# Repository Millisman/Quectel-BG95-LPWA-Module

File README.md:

# Quectel-BG95-LPWA-Module
Quectel BG95 LPWA Module board with integrated GPS &amp; GSM

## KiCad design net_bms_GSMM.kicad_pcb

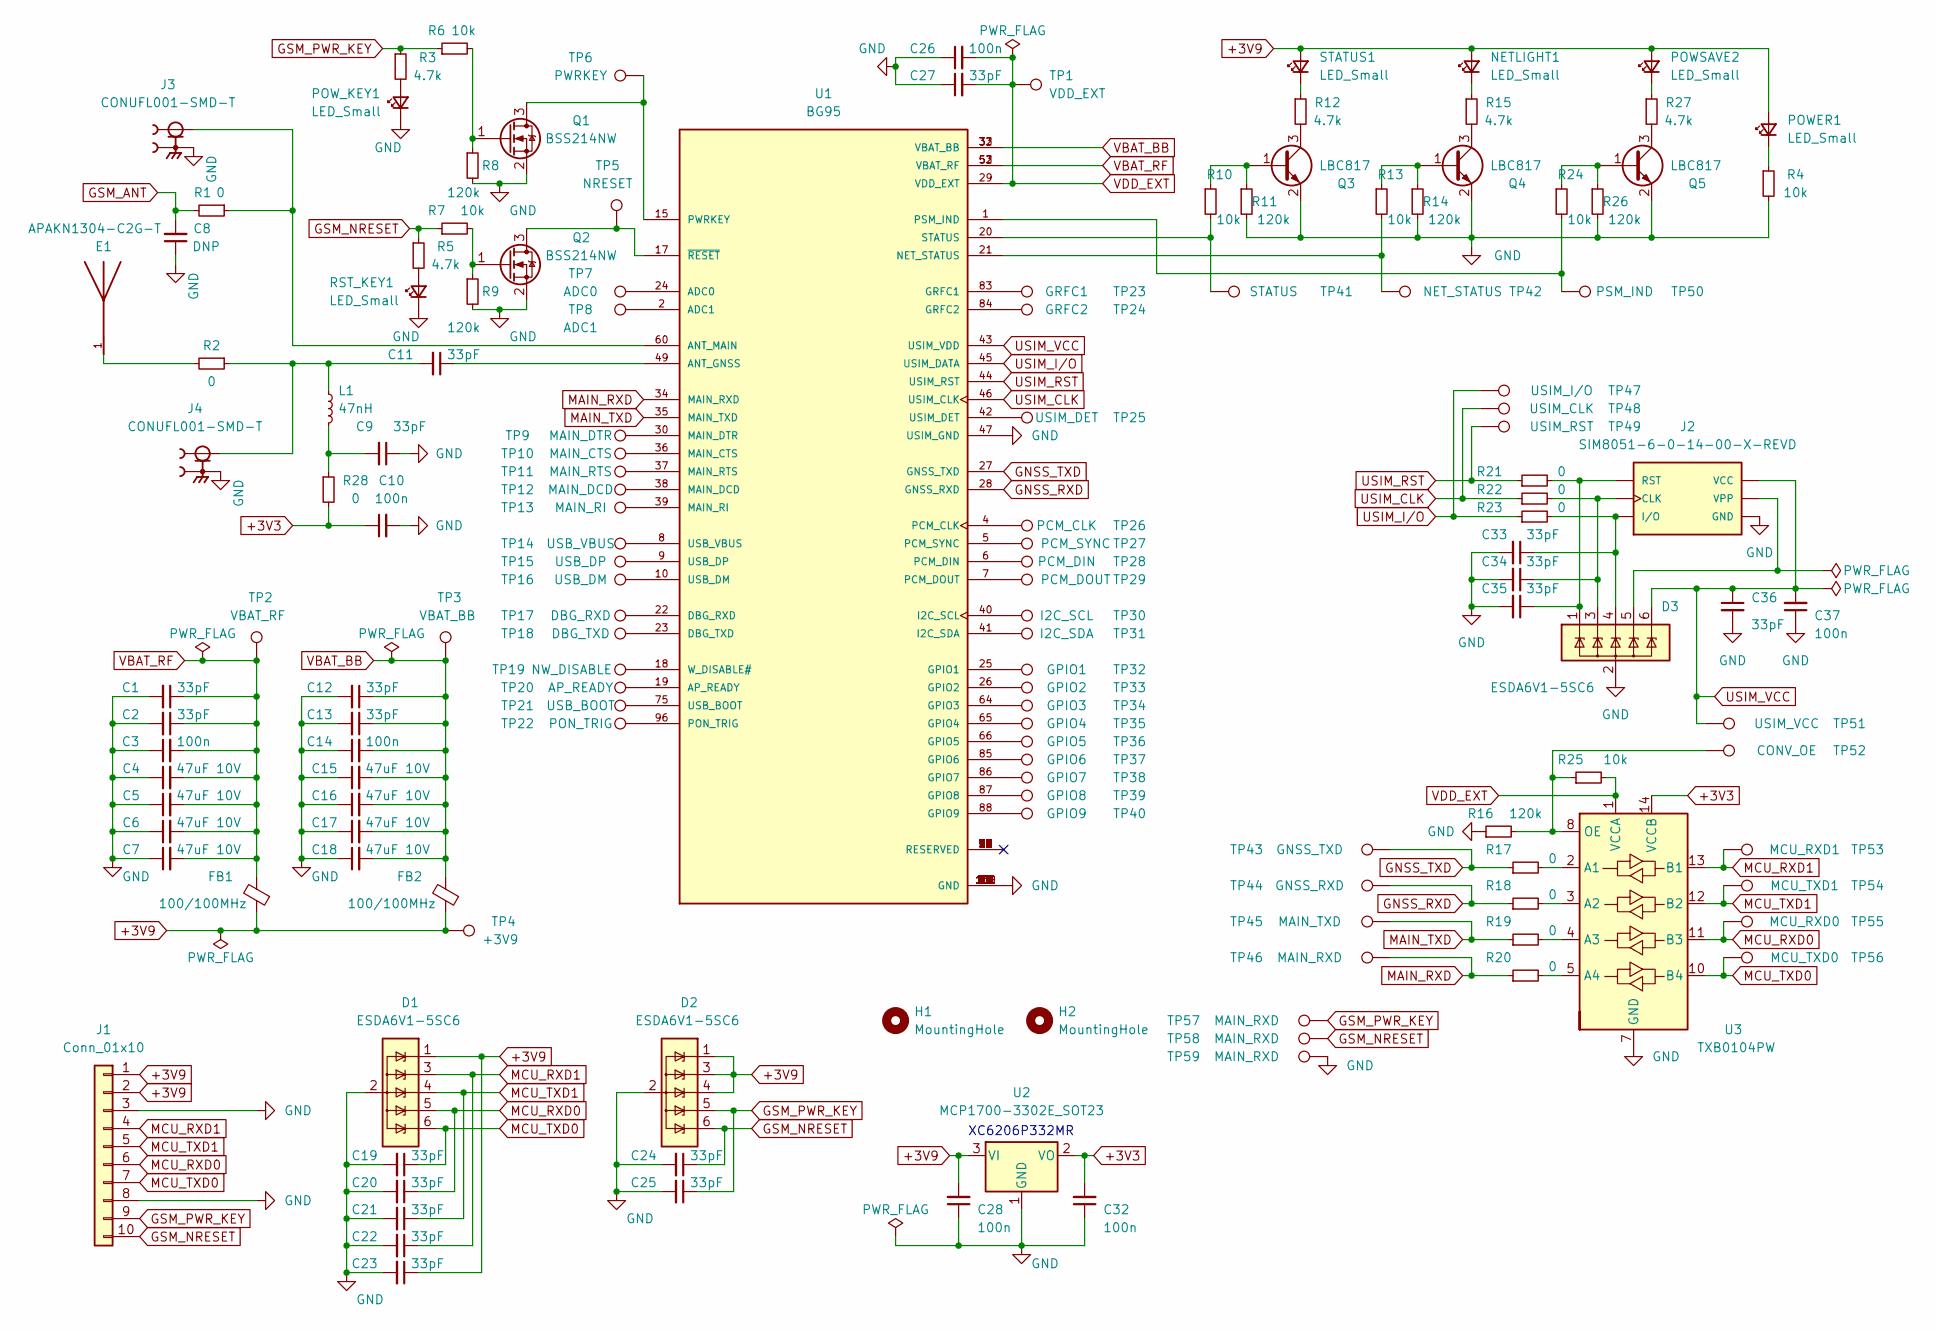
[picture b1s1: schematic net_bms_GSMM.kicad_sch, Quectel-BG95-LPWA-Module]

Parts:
C1, C2, C9, C11, C12, C13, C19, C20, C21, C22, C23, C24, C25, C27, C33, C34, C35, C36: 33pF; C_0402_1005Metric
C3, C10, C14, C26, C28, C32, C37: 100n; C_0402_1005Metric
C4, C5, C6, C7, C15, C16, C17, C18: 47uF 10V; C_1206_3216Metric
C8: DNP; C_0402_1005Metric
D1, D2, D3: ESDA6V1-5SC6; SOT-23-6
E1: APAKN1304-C2G-T; XCVR_APAKN1304-C2G-T; PARTREV 02.13.2020
FB1, FB2: 100/100MHz; R_0603_1608Metric
H1, H2: MountingHole; MountingHole_3.2mm_M3
J1: Conn_01x10; Wuerth_WR-WTB_64801011622_1x10_P1.50mm_Vertical
J2: SIM8051-6-0-14-00-X-REVD; GCT_SIM8051-6-0-14-00-X-REVD
J3, J4: CONUFL001-SMD-T; LINX_CONUFL001-SMD-T; PARTREV B
L1: 47nH; L_0402_1005Metric; LCSC C275325
NETLIGHT1: LED_Small; LED_0603_1608Metric
POWER1: LED_Small; LED_0603_1608Metric
POWSAVE2: LED_Small; LED_0603_1608Metric
POW_KEY1: LED_Small; LED_0603_1608Metric
Q1, Q2: BSS214NW; SOT-323_SC-70
Q3, Q4, Q5: LBC817; SOT-323_SC-70
R1, R2, R17, R18, R19, R20, R21, R22, R23, R28: 0; R_0402_1005Metric
R3, R5, R12, R15, R27: 4.7k; R_0402_1005Metric
R4, R6, R7, R10, R13, R24, R25: 10k; R_0402_1005Metric
R8, R9, R11, R14, R16, R26: 120k; R_0402_1005Metric
RST_KEY1: LED_Small; LED_0603_1608Metric
STATUS1: LED_Small; LED_0603_1608Metric
TP1: VDD_EXT; TestPoint_Pad_D1.0mm
TP2: VBAT_RF; TestPoint_Pad_D1.0mm
TP3: VBAT_BB; TestPoint_Pad_D1.0mm
TP4: +3V9; TestPoint_Pad_D1.0mm
TP5: NRESET; TestPoint_Pad_D1.0mm
TP6: PWRKEY; TestPoint_Pad_D1.0mm
TP7: ADC0; TestPoint_Pad_D1.0mm
TP8: ADC1; TestPoint_Pad_D1.0mm
TP9: MAIN_DTR; TestPoint_Pad_D1.0mm
TP10: MAIN_CTS; TestPoint_Pad_D1.0mm
TP11: MAIN_RTS; TestPoint_Pad_D1.0mm
TP12: MAIN_DCD; TestPoint_Pad_D1.0mm
TP13: MAIN_RI; TestPoint_Pad_D1.0mm
TP14: USB_VBUS; TestPoint_Pad_D1.0mm
TP15: USB_DP; TestPoint_Pad_D1.0mm
TP16: USB_DM; TestPoint_Pad_D1.0mm
TP17: DBG_RXD; TestPoint_Pad_D1.0mm
TP18: DBG_TXD; TestPoint_Pad_D1.0mm
TP19: NW_DISABLE; TestPoint_Pad_D1.0mm
TP20: AP_READY; TestPoint_Pad_D1.0mm
TP21: USB_BOOT; TestPoint_Pad_D1.0mm
TP22: PON_TRIG; TestPoint_Pad_D1.0mm
TP23: GRFC1; TestPoint_Pad_D1.0mm
TP24: GRFC2; TestPoint_Pad_D1.0mm
TP25: USIM_DET; TestPoint_Pad_D1.0mm
TP26: PCM_CLK; TestPoint_Pad_D1.0mm
TP27: PCM_SYNC; TestPoint_Pad_D1.0mm
TP28: PCM_DIN; TestPoint_Pad_D1.0mm
TP29: PCM_DOUT; TestPoint_Pad_D1.0mm
TP30: I2C_SCL; TestPoint_Pad_D1.0mm
TP31: I2C_SDA; TestPoint_Pad_D1.0mm
TP32: GPIO1; TestPoint_Pad_D1.0mm
TP33: GPIO2; TestPoint_Pad_D1.0mm
TP34: GPIO3; TestPoint_Pad_D1.0mm
TP35: GPIO4; TestPoint_Pad_D1.0mm
TP36: GPIO5; TestPoint_Pad_D1.0mm
TP37: GPIO6; TestPoint_Pad_D1.0mm
TP38: GPIO7; TestPoint_Pad_D1.0mm
TP39: GPIO8; TestPoint_Pad_D1.0mm
TP40: GPIO9; TestPoint_Pad_D1.0mm
TP41: STATUS; TestPoint_Pad_D1.0mm
TP42: NET_STATUS; TestPoint_Pad_D1.0mm
TP43: GNSS_TXD; TestPoint_Pad_D1.0mm
TP44: GNSS_RXD; TestPoint_Pad_D1.0mm
TP45: MAIN_TXD; TestPoint_Pad_D1.0mm
TP46, TP57, TP58, TP59: MAIN_RXD; TestPoint_Pad_D1.0mm
TP47: USIM_I/O; TestPoint_Pad_D1.0mm
TP48: USIM_CLK; TestPoint_Pad_D1.0mm
TP49: USIM_RST; TestPoint_Pad_D1.0mm
TP50: PSM_IND; TestPoint_Pad_D1.0mm
TP51: USIM_VCC; TestPoint_Pad_D1.0mm
TP52: CONV_OE; TestPoint_Pad_D1.0mm
TP53: MCU_RXD1; TestPoint_Pad_D1.0mm
TP54: MCU_TXD1; TestPoint_Pad_D1.0mm
TP55: MCU_RXD0; TestPoint_Pad_D1.0mm
TP56: MCU_TXD0; TestPoint_Pad_D1.0mm
U1: BG95; XCVR_BG95; PARTREV 1.1
U2: MCP1700-3302E_SOT23; SOT-23
U3: TXB0104PW; TSSOP-14_4.4x5mm_P0.65mm

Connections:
+3V3: C10.1, C32.2, R28.2, U2.2 (VO), U3.14 (VCCB)
+3V9: C23.1, C28.2, D1.1 (IO1), D2.1 (IO1), D2.3 (IO2), D2.4 (IO3), FB1.1, FB2.1, J1.1, J1.2, NETLIGHT1.2 (A), POWER1.2 (A), POWSAVE2.2 (A), STATUS1.2 (A), TP4.1, U2.3 (VI)
GND: C1.2, C2.2, C3.1, C4.1, C5.1, C6.1, C7.1, C8.1, C9.1, C10.2, C12.2, C13.2, C14.1, C15.1, C16.1, C17.1, C18.1, C19.2, C20.2, C21.2, C22.2, C23.2, C24.2, C25.2, C26.1, C27.1, C28.1, C32.1, C33.2, C34.2, C35.2, C36.2, C37.1, D1.2 (GND), D2.2 (GND), D3.2 (GND), E1.2, E1.3, E1.4, E1.5, E1.6, E1.7, E1.8, E1.9, J1.3, J1.8, J2.C4, J2.C5 (GND), J2.C8, J3.2, J3.3, J4.2, J4.3, POW_KEY1.1 (K), Q1.2 (S), Q2.2 (S), Q3.2 (E), Q4.2 (E), Q5.2 (E), R4.2, R8.2, R9.2, R11.2, R14.2, R16.1, R26.2, RST_KEY1.1 (K), TP59.1, U1.3 (GND), U1.31 (GND), U1.47 (USIM_GND), U1.48 (GND), U1.50 (GND), U1.54 (GND), U1.55 (GND), U1.58 (GND), U1.59 (GND), U1.61 (GND), U1.62 (GND), U1.67 (GND), U1.68 (GND), U1.69 (GND), U1.70 (GND), U1.71 (GND), U1.72 (GND), U1.73 (GND), U1.74 (GND), U1.79 (GND), U1.80 (GND), U1.81 (GND), U1.82 (GND), U1.89 (GND), U1.90 (GND), U1.91 (GND), U1.100 (GND), U1.101 (GND), U1.102 (GND), U2.1 (GND), U3.7 (GND)
GNSS_RXD: R18.1, TP44.1, U1.28 (GNSS_RXD)
GNSS_TXD: R17.1, TP43.1, U1.27 (GNSS_TXD)
GSM_ANT: C8.2, R1.2
GSM_NRESET: C24.1, D2.6 (IO5), J1.10, R5.1, R7.1, TP58.1
GSM_PWR_KEY: C25.1, D2.5 (IO4), J1.9, R3.1, R6.1, TP57.1
MAIN_RXD: R20.1, TP46.1, U1.34 (MAIN_RXD)
MAIN_TXD: R19.1, TP45.1, U1.35 (MAIN_TXD)
MCU_RXD0: C20.1, D1.5 (IO4), J1.6, TP55.1, U3.11 (B3)
MCU_RXD1: C22.1, D1.3 (IO2), J1.4, TP53.1, U3.13 (B1)
MCU_TXD0: C19.1, D1.6 (IO5), J1.7, TP56.1, U3.10 (B4)
MCU_TXD1: C21.1, D1.4 (IO3), J1.5, TP54.1, U3.12 (B2)
unnamed: C9.2, L1.2, R28.1
unnamed: C11.1, U1.49 (ANT_GNSS)
unnamed: C11.2, J4.1, L1.1, R2.1
unnamed: C33.1, D3.4 (IO3), J2.C7 (I/O), R23.2
unnamed: C34.1, D3.3 (IO2), J2.C3 (CLK), R22.2
unnamed: C35.1, D3.1 (IO1), J2.C2 (RST), R21.2
unnamed: D3.5 (IO4), J2.C6 (VPP)
unnamed: E1.1, R2.2
unnamed: J3.1, R1.1, U1.60 (ANT_MAIN)
unnamed: NETLIGHT1.1 (K), R15.1
unnamed: POWER1.1 (K), R4.1
unnamed: POWSAVE2.1 (K), R27.1
unnamed: POW_KEY1.2 (A), R3.2
unnamed: Q1.1 (G), R6.2, R8.1
unnamed: Q1.3 (D), TP6.1, U1.15 (PWRKEY)
unnamed: Q2.1 (G), R7.2, R9.1
unnamed: Q2.3 (D), TP5.1, U1.17 (~RESET)
unnamed: Q3.1 (B), R10.1, R11.1
unnamed: Q3.3 (C), R12.2
unnamed: Q4.1 (B), R13.1, R14.1
unnamed: Q4.3 (C), R15.2
unnamed: Q5.1 (B), R24.1, R26.1
unnamed: Q5.3 (C), R27.2
unnamed: R5.2, RST_KEY1.2 (A)
unnamed: R10.2, TP41.1, U1.20 (STATUS)
unnamed: R12.1, STATUS1.1 (K)
unnamed: R13.2, TP42.1, U1.21 (NET_STATUS)
unnamed: R16.2, R25.1, TP52.1, U3.8 (OE)
unnamed: R17.2, U3.2 (A1)
unnamed: R18.2, U3.3 (A2)
unnamed: R19.2, U3.4 (A3)
unnamed: R20.2, U3.5 (A4)
unnamed: R24.2, TP50.1, U1.1 (PSM_IND)
unnamed: TP7.1, U1.24 (ADC0)
unnamed: TP8.1, U1.2 (ADC1)
unnamed: TP9.1, U1.30 (MAIN_DTR)
unnamed: TP10.1, U1.36 (MAIN_CTS)
unnamed: TP11.1, U1.37 (MAIN_RTS)
unnamed: TP12.1, U1.38 (MAIN_DCD)
unnamed: TP13.1, U1.39 (MAIN_RI)
unnamed: TP14.1, U1.8 (USB_VBUS)
unnamed: TP15.1, U1.9 (USB_DP)
unnamed: TP16.1, U1.10 (USB_DM)
unnamed: TP17.1, U1.22 (DBG_RXD)
unnamed: TP18.1, U1.23 (DBG_TXD)
unnamed: TP19.1, U1.18 (W_DISABLE#)
unnamed: TP20.1, U1.19 (AP_READY)
unnamed: TP21.1, U1.75 (USB_BOOT)
unnamed: TP22.1, U1.96 (PON_TRIG)
unnamed: TP23.1, U1.83 (GRFC1)
unnamed: TP24.1, U1.84 (GRFC2)
unnamed: TP25.1, U1.42 (USIM_DET)
unnamed: TP26.1, U1.4 (PCM_CLK)
unnamed: TP27.1, U1.5 (PCM_SYNC)
unnamed: TP28.1, U1.6 (PCM_DIN)
unnamed: TP29.1, U1.7 (PCM_DOUT)
unnamed: TP30.1, U1.40 (I2C_SCL)
unnamed: TP31.1, U1.41 (I2C_SDA)
unnamed: TP32.1, U1.25 (GPIO1)
unnamed: TP33.1, U1.26 (GPIO2)
unnamed: TP34.1, U1.64 (GPIO3)
unnamed: TP35.1, U1.65 (GPIO4)
unnamed: TP36.1, U1.66 (GPIO5)
unnamed: TP37.1, U1.85 (GPIO6)
unnamed: TP38.1, U1.86 (GPIO7)
unnamed: TP39.1, U1.87 (GPIO8)
unnamed: TP40.1, U1.88 (GPIO9)
USIM_CLK: R22.1, TP48.1, U1.46 (USIM_CLK)
USIM_I/O: R23.1, TP47.1, U1.45 (USIM_DATA)
USIM_RST: R21.1, TP49.1, U1.44 (USIM_RST)
USIM_VCC: C36.1, C37.2, D3.6 (IO5), J2.C1 (VCC), TP51.1, U1.43 (USIM_VDD)
VBAT_BB: C12.1, C13.1, C14.2, C15.2, C16.2, C17.2, C18.2, FB2.2, TP3.1, U1.32 (VBAT_BB), U1.33 (VBAT_BB)
VBAT_RF: C1.1, C2.1, C3.2, C4.2, C5.2, C6.2, C7.2, FB1.2, TP2.1, U1.52 (VBAT_RF), U1.53 (VBAT_RF)
VDD_EXT: C26.2, C27.2, R25.2, TP1.1, U1.29 (VDD_EXT), U3.1 (VCCA)

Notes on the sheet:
XC6206P332MR

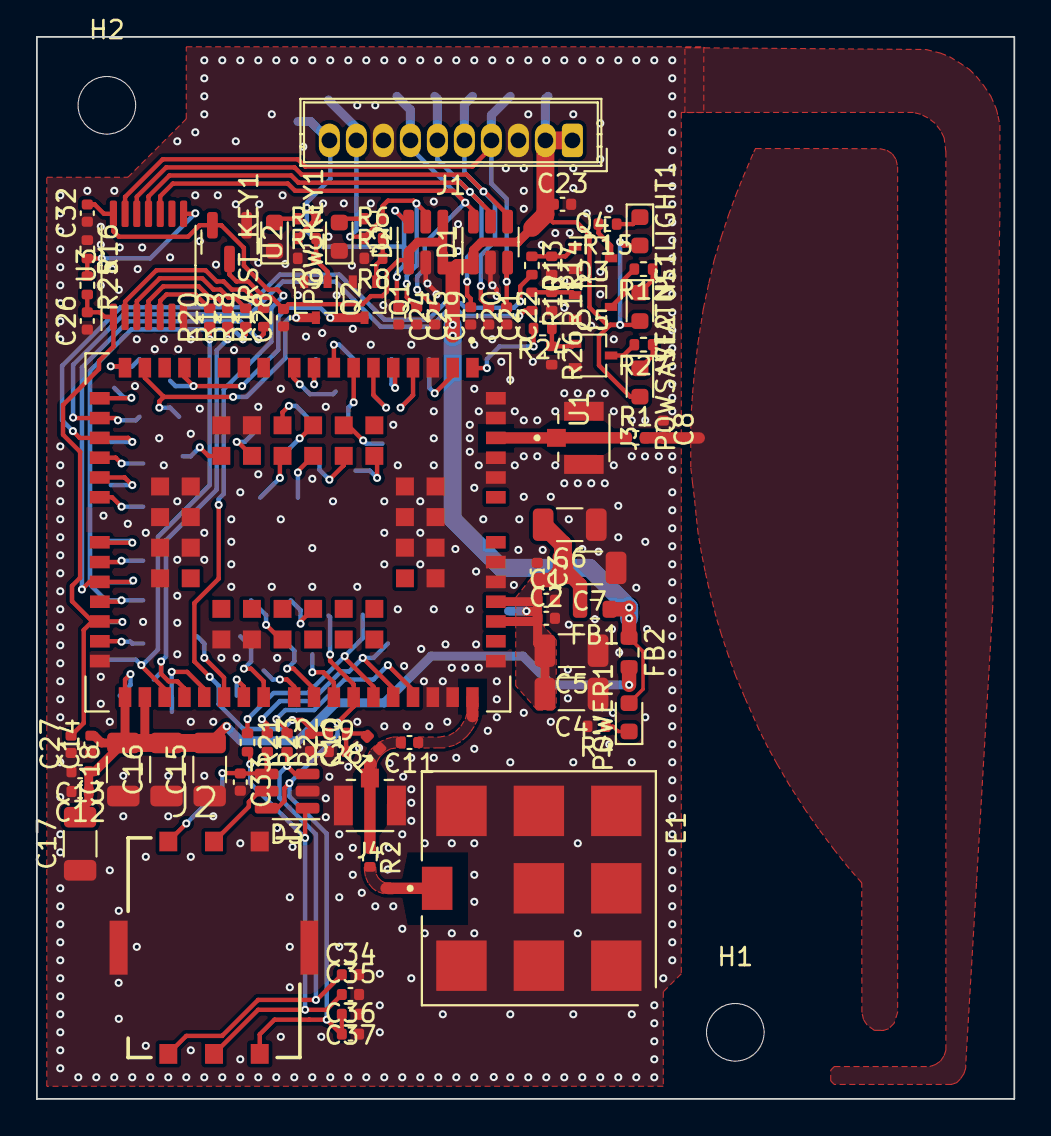
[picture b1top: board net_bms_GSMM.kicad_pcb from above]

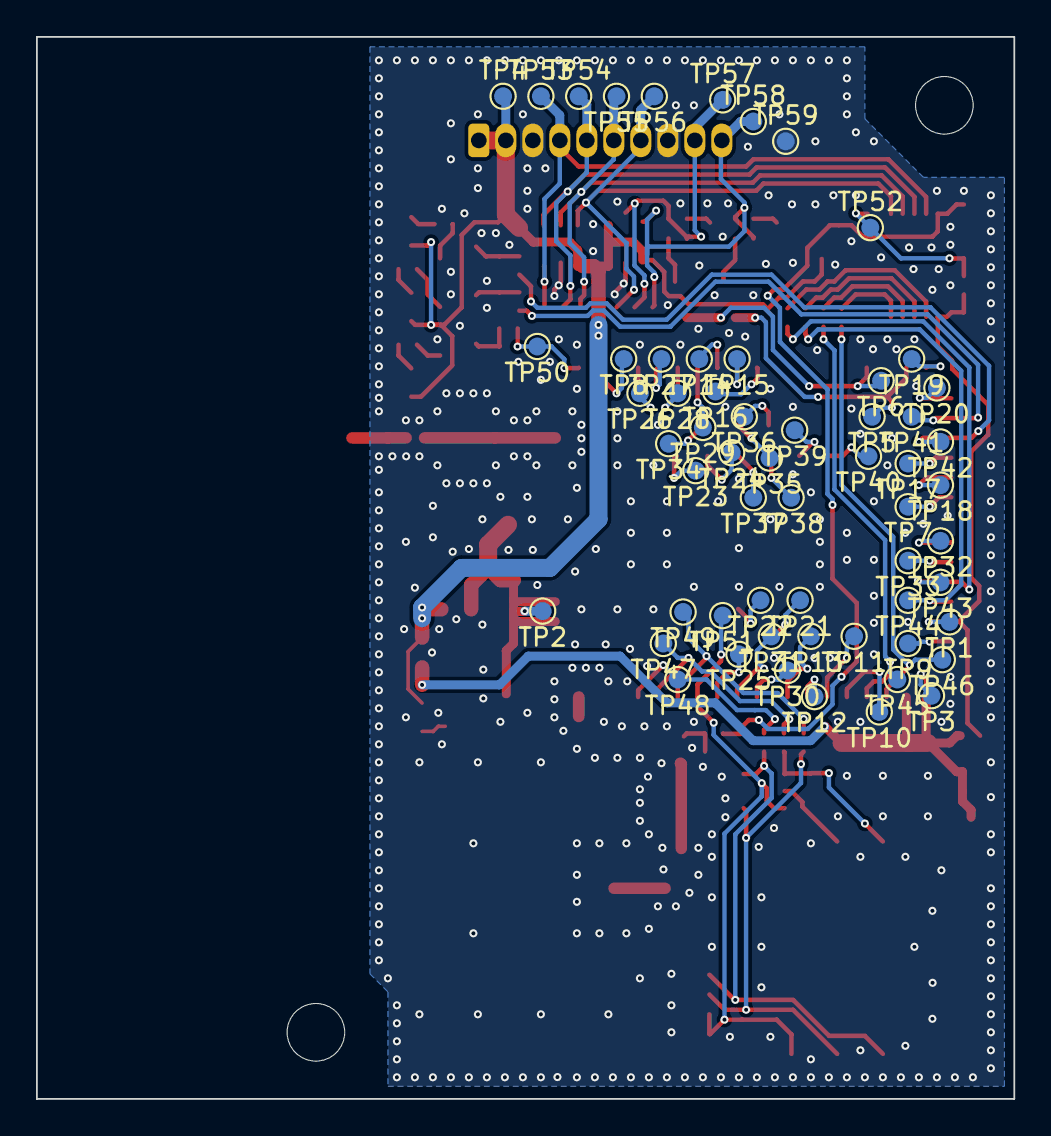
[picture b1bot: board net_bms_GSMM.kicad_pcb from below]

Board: 2 copper layers, 54.3 x 59.0 mm, 148 parts (59 on the bottom side), 88 nets.

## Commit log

2022-03-07 initial
